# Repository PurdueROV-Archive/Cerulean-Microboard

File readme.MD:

This is an example repository of the previous Microboard for the ROV.

The Microboard was the brains of the ROV.

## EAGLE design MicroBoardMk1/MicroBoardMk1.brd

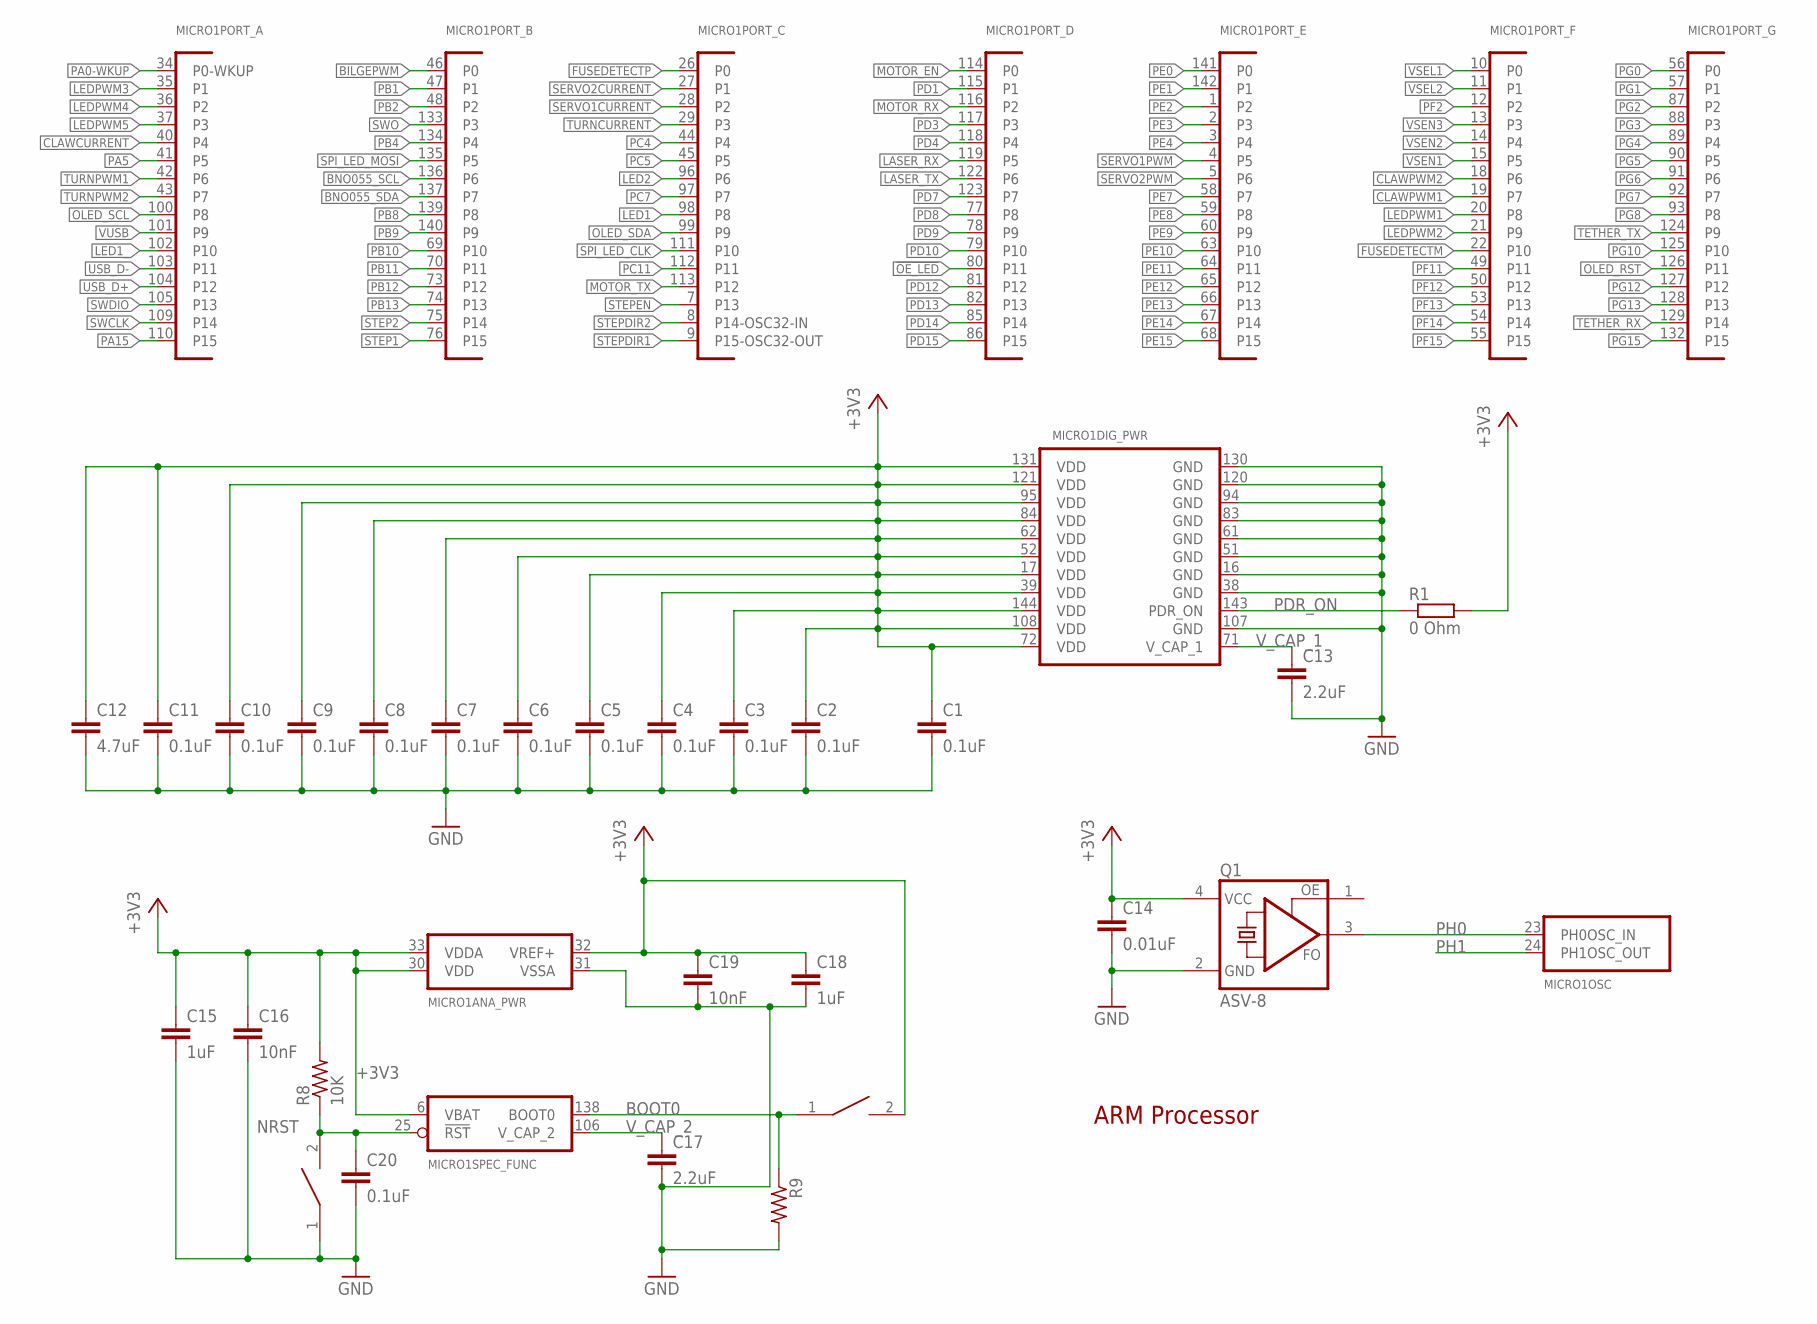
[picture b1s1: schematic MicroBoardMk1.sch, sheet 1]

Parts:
BOOT_SW: SWITCH; SW_2512
C1, C2, C3, C4, C5, C6, C7, C8, C9, C10, C11, C20: 0.1uF; C0603
C12: 4.7uF; C0603
C13, C17: 2.2uF; C0603
C14: 0.01uF; C0603
C15, C18: 1uF; C0603
C16, C19: 10nF; C0603
MICRO1: STM32F407ZET6; SQFP-S-20X20-144
Q1: ASV-8; ASF
R1: 0 Ohm; R0603
R8: 10K; R0603
R9: R-US_R0603; R0603
RST_SW: SWITCH; SW_2512

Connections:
!OE_LED: MICRO1.80 (P11); also elsewhere on the board
+3V3: BOOT_SW.2, C1.1, C2.1, C3.1, C4.1, C5.1, C6.1, C7.1, C8.1, C9.1, C10.1, C11.1, C12.1, C14.1, C15.1, C16.1, C18.1, C19.1, MICRO1.6 (VBAT), MICRO1.17 (VDD), MICRO1.30 (VDD), MICRO1.32 (VREF+), MICRO1.33 (VDDA), MICRO1.39 (VDD), MICRO1.52 (VDD), MICRO1.62 (VDD), MICRO1.72 (VDD), MICRO1.84 (VDD), MICRO1.95 (VDD), MICRO1.108 (VDD), MICRO1.121 (VDD), MICRO1.131 (VDD), MICRO1.144 (VDD), Q1.4 (VCC), R1.2, R8.2; also elsewhere on the board
BILGEPWM: MICRO1.46 (P0); also elsewhere on the board
BNO055_SCL: MICRO1.136 (P6); also elsewhere on the board
BNO055_SDA: MICRO1.137 (P7); also elsewhere on the board
BOOT0: BOOT_SW.1, MICRO1.138 (BOOT0), R9.1; also elsewhere on the board
CLAWCURRENT: MICRO1.40 (P4); also elsewhere on the board
CLAWPWM1: MICRO1.19 (P7); also elsewhere on the board
CLAWPWM2: MICRO1.18 (P6); also elsewhere on the board
FUSEDETECTM: MICRO1.22 (P10); also elsewhere on the board
FUSEDETECTP: MICRO1.26 (P0); also elsewhere on the board
GND: C1.2, C2.2, C3.2, C4.2, C5.2, C6.2, C7.2, C8.2, C9.2, C10.2, C11.2, C12.2, C13.2, C14.2, C15.2, C16.2, C17.2, C18.2, C19.2, C20.2, MICRO1.16 (GND), MICRO1.31 (VSSA), MICRO1.38 (GND), MICRO1.51 (GND), MICRO1.61 (GND), MICRO1.83 (GND), MICRO1.94 (GND), MICRO1.107 (GND), MICRO1.120 (GND), MICRO1.130 (GND), Q1.2 (GND), R9.2, RST_SW.1; also elsewhere on the board
LASER_RX: MICRO1.119 (P5); also elsewhere on the board
LASER_TX: MICRO1.122 (P6); also elsewhere on the board
LED1: MICRO1.98 (P8); also elsewhere on the board
LED1_: MICRO1.102 (P10); also elsewhere on the board
LED2: MICRO1.96 (P6); also elsewhere on the board
LEDPWM1: MICRO1.20 (P8); also elsewhere on the board
LEDPWM2: MICRO1.21 (P9); also elsewhere on the board
LEDPWM3: MICRO1.35 (P1); also elsewhere on the board
LEDPWM4: MICRO1.36 (P2); also elsewhere on the board
LEDPWM5: MICRO1.37 (P3); also elsewhere on the board
MOTOR_EN: MICRO1.114 (P0); also elsewhere on the board
MOTOR_RX: MICRO1.116 (P2); also elsewhere on the board
MOTOR_TX: MICRO1.113 (P12); also elsewhere on the board
NRST: C20.1, MICRO1.25 (!RST), R8.1, RST_SW.2; also elsewhere on the board
OLED_RST: MICRO1.126 (P11); also elsewhere on the board
OLED_SCL: MICRO1.100 (P8); also elsewhere on the board
OLED_SDA: MICRO1.99 (P9); also elsewhere on the board
PA0-WKUP: MICRO1.34 (P0-WKUP); also elsewhere on the board
PA5: MICRO1.41 (P5); also elsewhere on the board
PA15: MICRO1.110 (P15); also elsewhere on the board
PB1: MICRO1.47 (P1); also elsewhere on the board
PB2: MICRO1.48 (P2); also elsewhere on the board
PB4: MICRO1.134 (P4); also elsewhere on the board
PB8: MICRO1.139 (P8); also elsewhere on the board
PB9: MICRO1.140 (P9); also elsewhere on the board
PB10: MICRO1.69 (P10); also elsewhere on the board
PB11: MICRO1.70 (P11); also elsewhere on the board
PB12: MICRO1.73 (P12); also elsewhere on the board
PB13: MICRO1.74 (P13); also elsewhere on the board
PC4: MICRO1.44 (P4); also elsewhere on the board
PC5: MICRO1.45 (P5); also elsewhere on the board
PC7: MICRO1.97 (P7); also elsewhere on the board
PC11: MICRO1.112 (P11); also elsewhere on the board
PD1: MICRO1.115 (P1); also elsewhere on the board
PD3: MICRO1.117 (P3); also elsewhere on the board
PD4: MICRO1.118 (P4); also elsewhere on the board
PD7: MICRO1.123 (P7); also elsewhere on the board
PD8: MICRO1.77 (P8); also elsewhere on the board
PD9: MICRO1.78 (P9); also elsewhere on the board
PD10: MICRO1.79 (P10); also elsewhere on the board
PD12: MICRO1.81 (P12); also elsewhere on the board
PD13: MICRO1.82 (P13); also elsewhere on the board
PD14: MICRO1.85 (P14); also elsewhere on the board
PD15: MICRO1.86 (P15); also elsewhere on the board
PDR_ON: MICRO1.143 (PDR_ON), R1.1; also elsewhere on the board
PE0: MICRO1.141 (P0); also elsewhere on the board
PE1: MICRO1.142 (P1); also elsewhere on the board
PE2: MICRO1.1 (P2); also elsewhere on the board
PE3: MICRO1.2 (P3); also elsewhere on the board
PE4: MICRO1.3 (P4); also elsewhere on the board
PE7: MICRO1.58 (P7); also elsewhere on the board
PE8: MICRO1.59 (P8); also elsewhere on the board
PE9: MICRO1.60 (P9); also elsewhere on the board
PE10: MICRO1.63 (P10); also elsewhere on the board
PE11: MICRO1.64 (P11); also elsewhere on the board
PE12: MICRO1.65 (P12); also elsewhere on the board
PE13: MICRO1.66 (P13); also elsewhere on the board
PE14: MICRO1.67 (P14); also elsewhere on the board
PE15: MICRO1.68 (P15); also elsewhere on the board
PF2: MICRO1.12 (P2); also elsewhere on the board
PF11: MICRO1.49 (P11); also elsewhere on the board
PF12: MICRO1.50 (P12); also elsewhere on the board
PF13: MICRO1.53 (P13); also elsewhere on the board
PF14: MICRO1.54 (P14); also elsewhere on the board
PF15: MICRO1.55 (P15); also elsewhere on the board
PG0: MICRO1.56 (P0); also elsewhere on the board
PG1: MICRO1.57 (P1); also elsewhere on the board
PG2: MICRO1.87 (P2); also elsewhere on the board
PG3: MICRO1.88 (P3); also elsewhere on the board
PG4: MICRO1.89 (P4); also elsewhere on the board
PG5: MICRO1.90 (P5); also elsewhere on the board
PG6: MICRO1.91 (P6); also elsewhere on the board
PG7: MICRO1.92 (P7); also elsewhere on the board
PG8: MICRO1.93 (P8); also elsewhere on the board
PG10: MICRO1.125 (P10); also elsewhere on the board
PG12: MICRO1.127 (P12); also elsewhere on the board
PG13: MICRO1.128 (P13); also elsewhere on the board
PG15: MICRO1.132 (P15); also elsewhere on the board
PH0: MICRO1.23 (PH0OSC_IN), Q1.3 (FO); also elsewhere on the board
PH1: MICRO1.24 (PH1OSC_OUT); also elsewhere on the board
SERVO1CURRENT: MICRO1.28 (P2); also elsewhere on the board
SERVO1PWM: MICRO1.4 (P5); also elsewhere on the board
SERVO2CURRENT: MICRO1.27 (P1); also elsewhere on the board
SERVO2PWM: MICRO1.5 (P6); also elsewhere on the board
SPI_LED_CLK: MICRO1.111 (P10); also elsewhere on the board
SPI_LED_MOSI: MICRO1.135 (P5); also elsewhere on the board
STEP1: MICRO1.76 (P15); also elsewhere on the board
STEP2: MICRO1.75 (P14); also elsewhere on the board
STEPDIR1: MICRO1.9 (P15-OSC32-OUT); also elsewhere on the board
STEPDIR2: MICRO1.8 (P14-OSC32-IN); also elsewhere on the board
STEPEN: MICRO1.7 (P13); also elsewhere on the board
SWCLK: MICRO1.109 (P14); also elsewhere on the board
SWDIO: MICRO1.105 (P13); also elsewhere on the board
SWO: MICRO1.133 (P3); also elsewhere on the board
TETHER_RX: MICRO1.129 (P14); also elsewhere on the board
TETHER_TX: MICRO1.124 (P9); also elsewhere on the board
TURNCURRENT: MICRO1.29 (P3); also elsewhere on the board
TURNPWM1: MICRO1.42 (P6); also elsewhere on the board
TURNPWM2: MICRO1.43 (P7); also elsewhere on the board
USB_D+: MICRO1.104 (P12); also elsewhere on the board
USB_D-: MICRO1.103 (P11); also elsewhere on the board
VSEL1: MICRO1.10 (P0); also elsewhere on the board
VSEL2: MICRO1.11 (P1); also elsewhere on the board
VSEN1: MICRO1.15 (P5); also elsewhere on the board
VSEN2: MICRO1.14 (P4); also elsewhere on the board
VSEN3: MICRO1.13 (P3); also elsewhere on the board
VUSB: MICRO1.101 (P9); also elsewhere on the board
V_CAP_1: C13.1, MICRO1.71 (V_CAP_1); also elsewhere on the board
V_CAP_2: C17.1, MICRO1.106 (V_CAP_2); also elsewhere on the board

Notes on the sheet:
ARM Processor

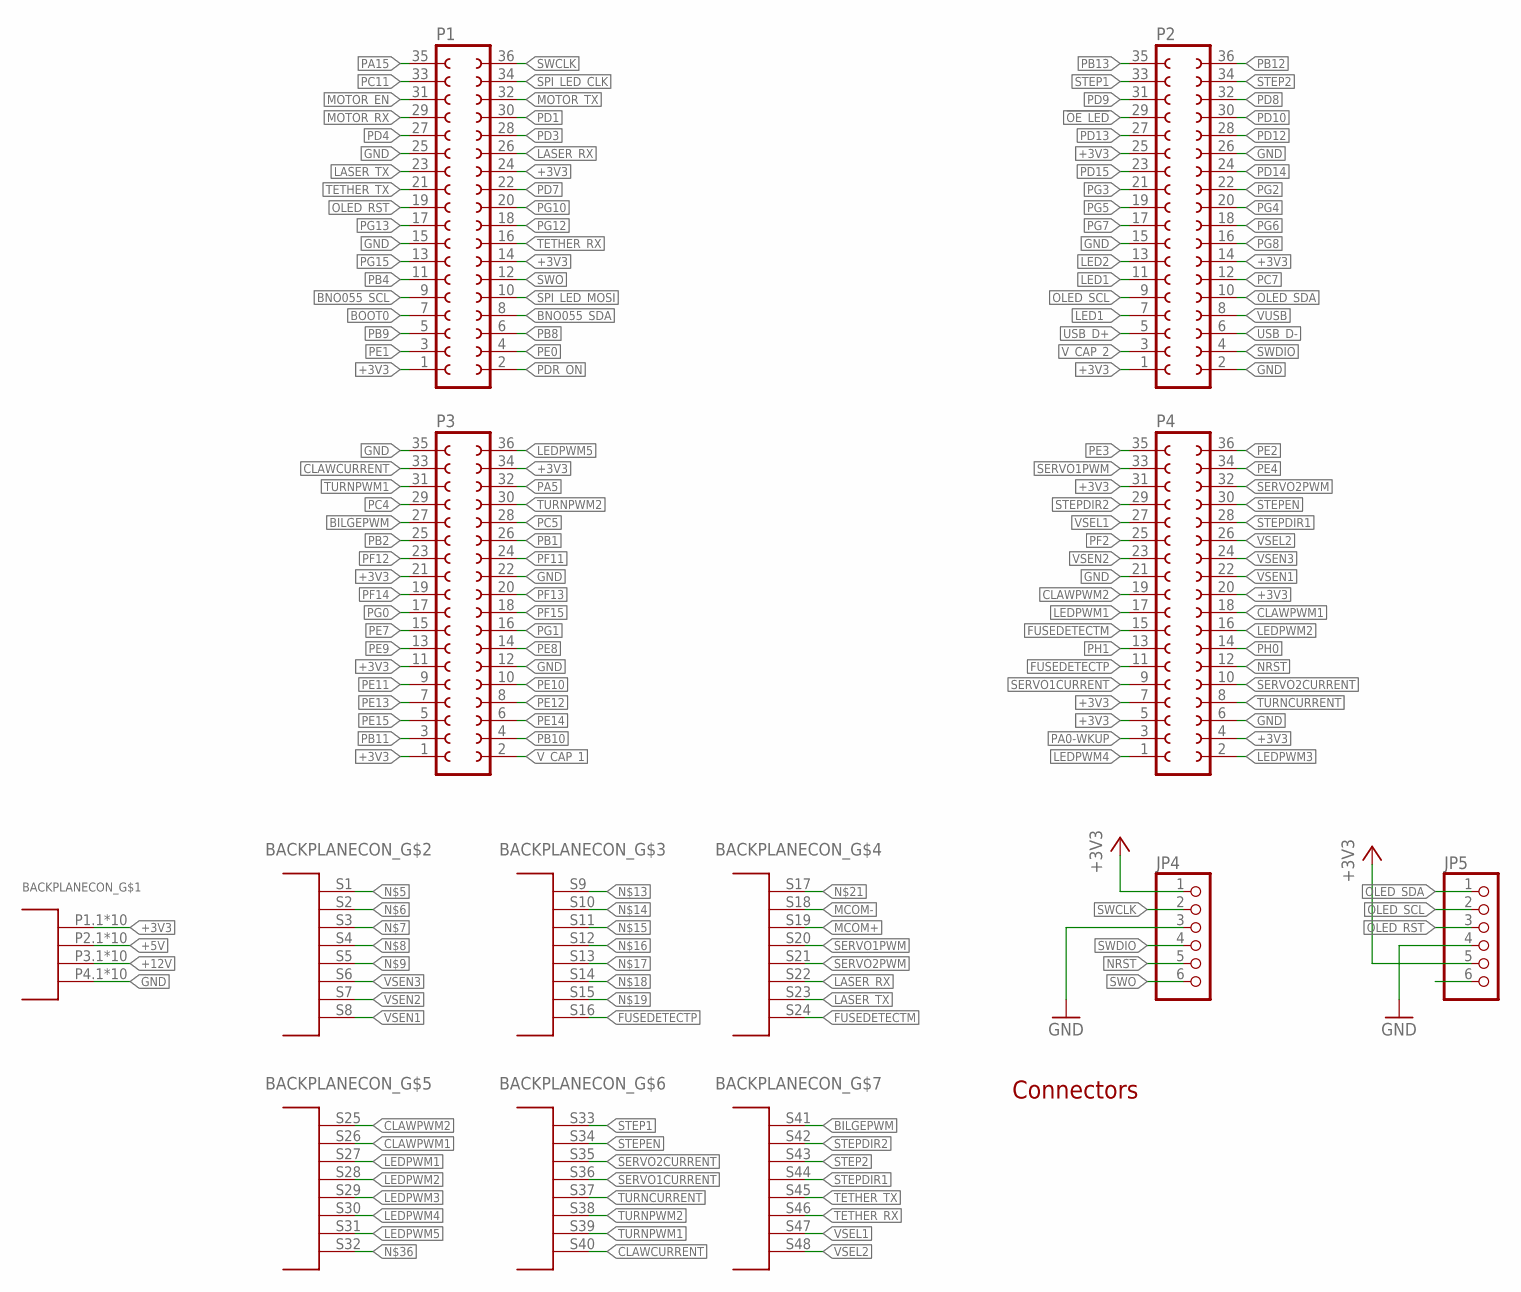
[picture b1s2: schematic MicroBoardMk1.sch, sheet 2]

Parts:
BACKPLANECON_: TEN60-S24-S24-P4-RA
JP4, JP5: PINHD-1X6; 1X06
P1, P2, P3, P4: FE18-2

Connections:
!OE_LED: P2.29; also elsewhere on the board
+3V3: BACKPLANECON_.P1.1, BACKPLANECON_.P1.2, BACKPLANECON_.P1.3, BACKPLANECON_.P1.4, BACKPLANECON_.P1.5, BACKPLANECON_.P1.6, BACKPLANECON_.P1.7, BACKPLANECON_.P1.8, BACKPLANECON_.P1.9, BACKPLANECON_.P1.10, JP4.1, JP5.5, P1.1, P1.14, P1.24, P2.1, P2.14, P2.25, P3.1, P3.11, P3.21, P3.34, P4.4, P4.5, P4.7, P4.20, P4.31; also elsewhere on the board
+5V: BACKPLANECON_.P2.1, BACKPLANECON_.P2.2, BACKPLANECON_.P2.3, BACKPLANECON_.P2.4, BACKPLANECON_.P2.5, BACKPLANECON_.P2.6, BACKPLANECON_.P2.7, BACKPLANECON_.P2.8, BACKPLANECON_.P2.9, BACKPLANECON_.P2.10; also elsewhere on the board
+12V: BACKPLANECON_.P3.1, BACKPLANECON_.P3.2, BACKPLANECON_.P3.3, BACKPLANECON_.P3.4, BACKPLANECON_.P3.5, BACKPLANECON_.P3.6, BACKPLANECON_.P3.7, BACKPLANECON_.P3.8, BACKPLANECON_.P3.9, BACKPLANECON_.P3.10
BILGEPWM: BACKPLANECON_.S41, P3.27; also elsewhere on the board
BNO055_SCL: P1.9; also elsewhere on the board
BNO055_SDA: P1.8; also elsewhere on the board
BOOT0: P1.7; also elsewhere on the board
CLAWCURRENT: BACKPLANECON_.S40, P3.33; also elsewhere on the board
CLAWPWM1: BACKPLANECON_.S26, P4.18; also elsewhere on the board
CLAWPWM2: BACKPLANECON_.S25, P4.19; also elsewhere on the board
FUSEDETECTM: BACKPLANECON_.S24, P4.15; also elsewhere on the board
FUSEDETECTP: BACKPLANECON_.S16, P4.11; also elsewhere on the board
GND: BACKPLANECON_.P4.1, BACKPLANECON_.P4.2, BACKPLANECON_.P4.3, BACKPLANECON_.P4.4, BACKPLANECON_.P4.5, BACKPLANECON_.P4.6, BACKPLANECON_.P4.7, BACKPLANECON_.P4.8, BACKPLANECON_.P4.9, BACKPLANECON_.P4.10, JP4.3, JP5.4, P1.15, P1.25, P2.2, P2.15, P2.26, P3.12, P3.22, P3.35, P4.6, P4.21; also elsewhere on the board
LASER_RX: BACKPLANECON_.S22, P1.26; also elsewhere on the board
LASER_TX: BACKPLANECON_.S23, P1.23; also elsewhere on the board
LED1: P2.11; also elsewhere on the board
LED1_: P2.7; also elsewhere on the board
LED2: P2.13; also elsewhere on the board
LEDPWM1: BACKPLANECON_.S27, P4.17; also elsewhere on the board
LEDPWM2: BACKPLANECON_.S28, P4.16; also elsewhere on the board
LEDPWM3: BACKPLANECON_.S29, P4.2; also elsewhere on the board
LEDPWM4: BACKPLANECON_.S30, P4.1; also elsewhere on the board
LEDPWM5: BACKPLANECON_.S31, P3.36; also elsewhere on the board
MCOM+: BACKPLANECON_.S19; also elsewhere on the board
MCOM-: BACKPLANECON_.S18; also elsewhere on the board
MOTOR_EN: P1.31; also elsewhere on the board
MOTOR_RX: P1.29; also elsewhere on the board
MOTOR_TX: P1.32; also elsewhere on the board
NRST: JP4.5, P4.12; also elsewhere on the board
OLED_RST: JP5.3, P1.19; also elsewhere on the board
OLED_SCL: JP5.2, P2.9; also elsewhere on the board
OLED_SDA: JP5.1, P2.10; also elsewhere on the board
PA0-WKUP: P4.3; also elsewhere on the board
PA5: P3.32; also elsewhere on the board
PA15: P1.35; also elsewhere on the board
PB1: P3.26; also elsewhere on the board
PB2: P3.25; also elsewhere on the board
PB4: P1.11; also elsewhere on the board
PB8: P1.6; also elsewhere on the board
PB9: P1.5; also elsewhere on the board
PB10: P3.4; also elsewhere on the board
PB11: P3.3; also elsewhere on the board
PB12: P2.36; also elsewhere on the board
PB13: P2.35; also elsewhere on the board
PC4: P3.29; also elsewhere on the board
PC5: P3.28; also elsewhere on the board
PC7: P2.12; also elsewhere on the board
PC11: P1.33; also elsewhere on the board
PD1: P1.30; also elsewhere on the board
PD3: P1.28; also elsewhere on the board
PD4: P1.27; also elsewhere on the board
PD7: P1.22; also elsewhere on the board
PD8: P2.32; also elsewhere on the board
PD9: P2.31; also elsewhere on the board
PD10: P2.30; also elsewhere on the board
PD12: P2.28; also elsewhere on the board
PD13: P2.27; also elsewhere on the board
PD14: P2.24; also elsewhere on the board
PD15: P2.23; also elsewhere on the board
PDR_ON: P1.2; also elsewhere on the board
PE0: P1.4; also elsewhere on the board
PE1: P1.3; also elsewhere on the board
PE2: P4.36; also elsewhere on the board
PE3: P4.35; also elsewhere on the board
PE4: P4.34; also elsewhere on the board
PE7: P3.15; also elsewhere on the board
PE8: P3.14; also elsewhere on the board
PE9: P3.13; also elsewhere on the board
PE10: P3.10; also elsewhere on the board
PE11: P3.9; also elsewhere on the board
PE12: P3.8; also elsewhere on the board
PE13: P3.7; also elsewhere on the board
PE14: P3.6; also elsewhere on the board
PE15: P3.5; also elsewhere on the board
PF2: P4.25; also elsewhere on the board
PF11: P3.24; also elsewhere on the board
PF12: P3.23; also elsewhere on the board
PF13: P3.20; also elsewhere on the board
PF14: P3.19; also elsewhere on the board
PF15: P3.18; also elsewhere on the board
PG0: P3.17; also elsewhere on the board
PG1: P3.16; also elsewhere on the board
PG2: P2.22; also elsewhere on the board
PG3: P2.21; also elsewhere on the board
PG4: P2.20; also elsewhere on the board
PG5: P2.19; also elsewhere on the board
PG6: P2.18; also elsewhere on the board
PG7: P2.17; also elsewhere on the board
PG8: P2.16; also elsewhere on the board
PG10: P1.20; also elsewhere on the board
PG12: P1.18; also elsewhere on the board
PG13: P1.17; also elsewhere on the board
PG15: P1.13; also elsewhere on the board
PH0: P4.14; also elsewhere on the board
PH1: P4.13; also elsewhere on the board
SERVO1CURRENT: BACKPLANECON_.S36, P4.9; also elsewhere on the board
SERVO1PWM: BACKPLANECON_.S20, P4.33; also elsewhere on the board
SERVO2CURRENT: BACKPLANECON_.S35, P4.10; also elsewhere on the board
SERVO2PWM: BACKPLANECON_.S21, P4.32; also elsewhere on the board
SPI_LED_CLK: P1.34; also elsewhere on the board
SPI_LED_MOSI: P1.10; also elsewhere on the board
STEP1: BACKPLANECON_.S33, P2.33; also elsewhere on the board
STEP2: BACKPLANECON_.S43, P2.34; also elsewhere on the board
STEPDIR1: BACKPLANECON_.S44, P4.28; also elsewhere on the board
STEPDIR2: BACKPLANECON_.S42, P4.29; also elsewhere on the board
STEPEN: BACKPLANECON_.S34, P4.30; also elsewhere on the board
SWCLK: JP4.2, P1.36; also elsewhere on the board
SWDIO: JP4.4, P2.4; also elsewhere on the board
SWO: JP4.6, P1.12; also elsewhere on the board
TETHER_RX: BACKPLANECON_.S46, P1.16; also elsewhere on the board
TETHER_TX: BACKPLANECON_.S45, P1.21; also elsewhere on the board
TURNCURRENT: BACKPLANECON_.S37, P4.8; also elsewhere on the board
TURNPWM1: BACKPLANECON_.S39, P3.31; also elsewhere on the board
TURNPWM2: BACKPLANECON_.S38, P3.30; also elsewhere on the board
USB_D+: P2.5; also elsewhere on the board
USB_D-: P2.6; also elsewhere on the board
VSEL1: BACKPLANECON_.S47, P4.27; also elsewhere on the board
VSEL2: BACKPLANECON_.S48, P4.26; also elsewhere on the board
VSEN1: BACKPLANECON_.S8, P4.22; also elsewhere on the board
VSEN2: BACKPLANECON_.S7, P4.23; also elsewhere on the board
VSEN3: BACKPLANECON_.S6, P4.24; also elsewhere on the board
VUSB: P2.8; also elsewhere on the board
V_CAP_1: P3.2; also elsewhere on the board
V_CAP_2: P2.3; also elsewhere on the board

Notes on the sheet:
Connectors

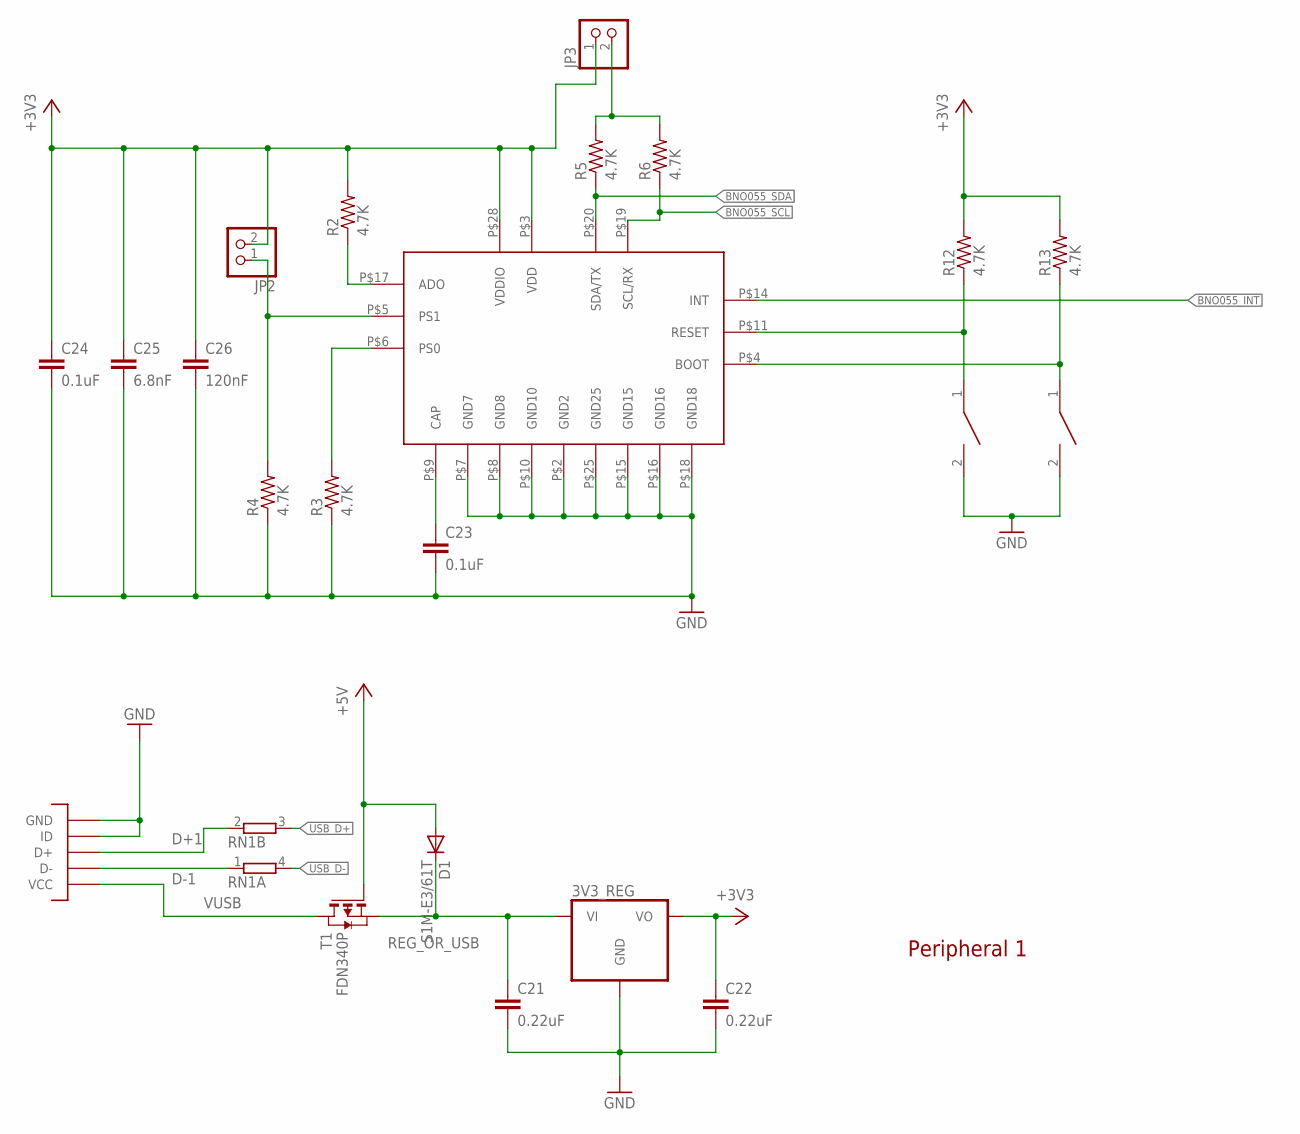
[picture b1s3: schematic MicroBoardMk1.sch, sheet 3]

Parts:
3V3_REG: AP1117-3.3SOT223; SOT223
BNO055: BNO055; LGA28
BNO_BOOT_SW: SWITCH; SW_2512
BNO_RST_SW: SWITCH; SW_2512
C21, C22: 0.22uF; C0603
C23, C24: 0.1uF; C0603
C25: 6.8nF; C0603
C26: 120nF; C0603
D1: S1M-E3/61T; DO-214AC
JP1: MICROUSB; MICRO_B
JP2, JP3: PINHD-1X2; 1X02
R2, R3, R4, R5, R6, R12, R13: 4.7K; R0603
RN1: 2R-NEXBV4V; EXBV4V
T1: FDN340P; SOT-23

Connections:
+3V3: 3V3_REG.2 (VO), 3V3_REG.4 (VO), BNO055.P$3 (VDD), BNO055.P$28 (VDDIO), C22.1, C24.1, C25.1, C26.1, JP2.2, JP3.1, R2.2, R12.2, R13.2; also elsewhere on the board
+5V: D1.A, T1.3 (G); also elsewhere on the board
BNO055_INT: BNO055.P$14 (INT)
BNO055_SCL: BNO055.P$19 (SCL/RX), R6.1; also elsewhere on the board
BNO055_SDA: BNO055.P$20 (SDA/TX), R5.1; also elsewhere on the board
D+1: JP1.P3 (D+), RN1.2 (1)
D-1: JP1.P2 (D-), RN1.1
GND: 3V3_REG.1 (GND), BNO055.P$2 (GND2), BNO055.P$7 (GND7), BNO055.P$8 (GND8), BNO055.P$10 (GND10), BNO055.P$15 (GND15), BNO055.P$16 (GND16), BNO055.P$18 (GND18), BNO055.P$25 (GND25), BNO_BOOT_SW.2, BNO_RST_SW.2, C21.2, C22.2, C23.2, C24.2, C25.2, C26.2, JP1.GND1 (GND), JP1.GND2 (GND), JP1.GND3 (GND), JP1.GND4 (GND), JP1.GND7 (GND), JP1.GND8 (GND), JP1.P4 (ID), JP1.P5 (GND), R3.1, R4.1; also elsewhere on the board
unnamed: BNO055.P$9 (CAP), C23.1
unnamed: BNO055.P$17 (ADO), R2.1
unnamed: BNO055.P$5 (PS1), JP2.1, R4.2
unnamed: BNO055.P$6 (PS0), R3.2
unnamed: JP3.2, R5.2, R6.2
unnamed: BNO055.P$4 (BOOT), BNO_BOOT_SW.1, R13.1
unnamed: BNO055.P$11 (RESET), BNO_RST_SW.1, R12.1
REG_OR_USB: 3V3_REG.3 (VI), C21.1, D1.C, T1.2 (S)
USB_D+: RN1.3 (2); also elsewhere on the board
USB_D-: RN1.4 (2); also elsewhere on the board
VUSB: JP1.P1 (VCC), T1.1 (D); also elsewhere on the board

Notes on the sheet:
Peripheral 1

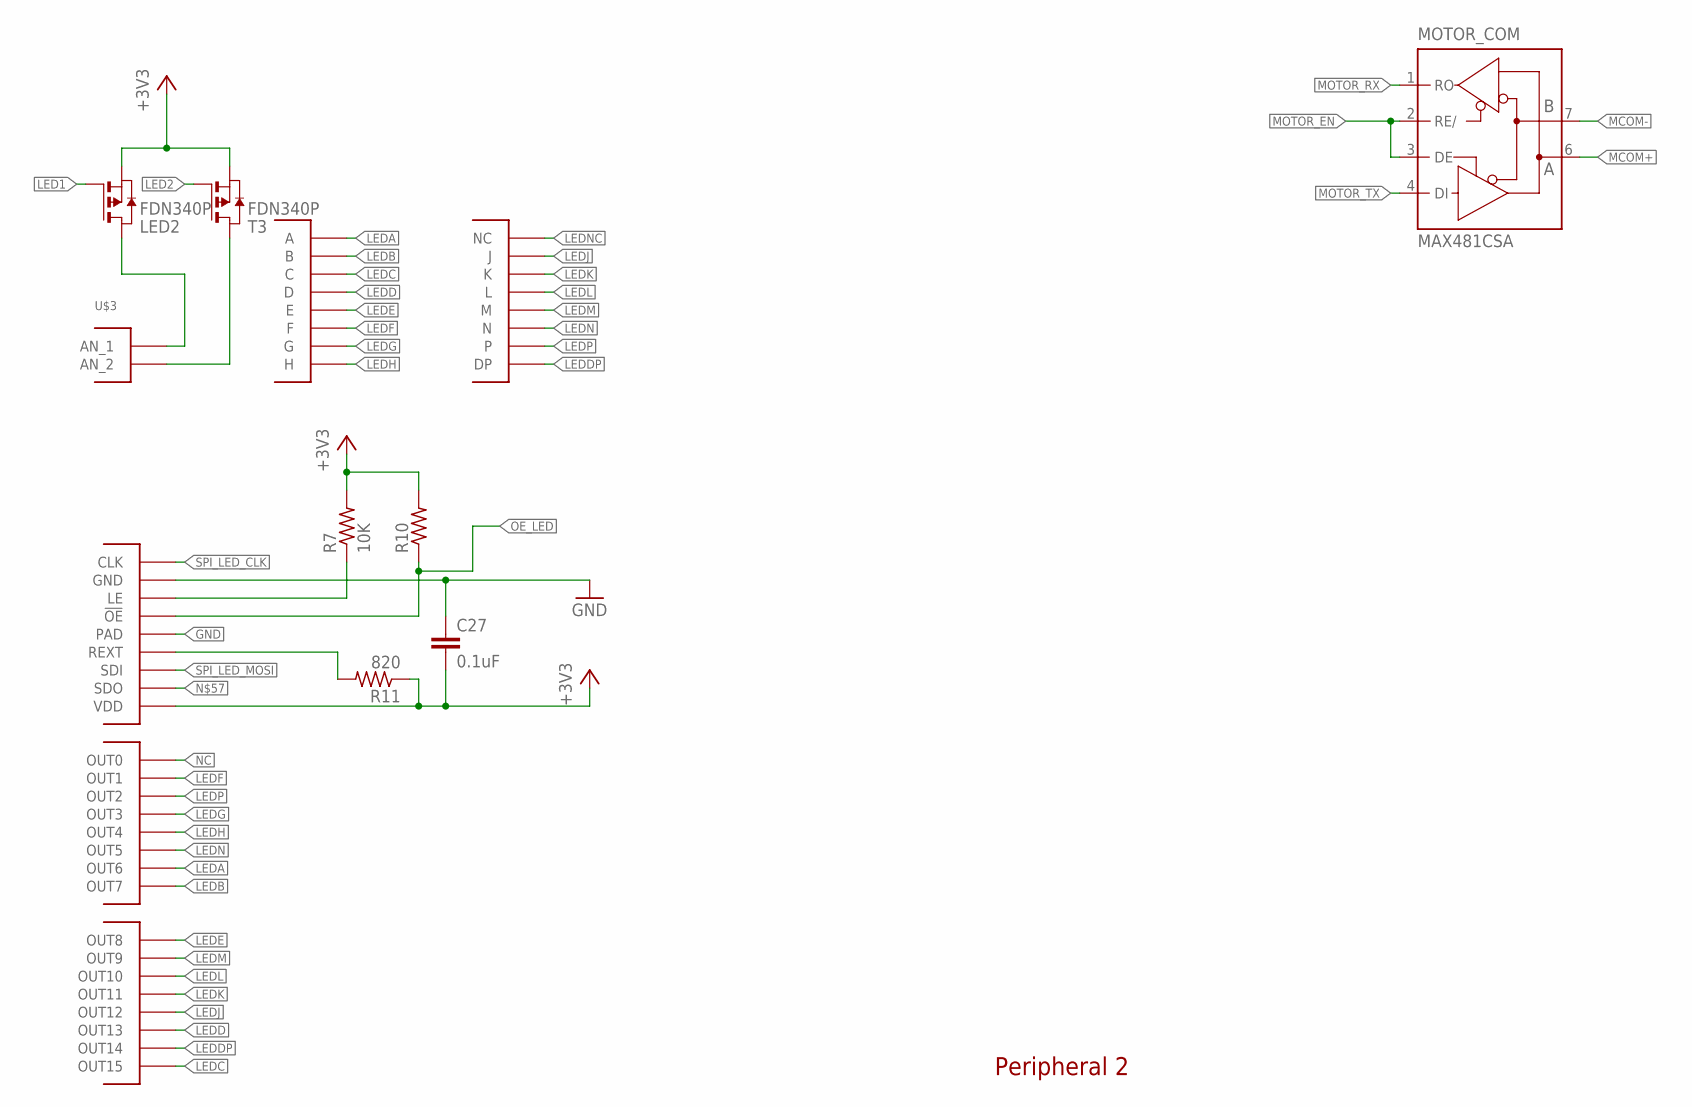
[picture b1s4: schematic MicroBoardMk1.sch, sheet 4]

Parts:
A6282: A6282; TSSOP24
C27: 0.1uF; C0603
LED2: FDN340P; SOT-23
MOTOR_COM: MAX481CSA; SO08
R7: 10K; R0603
R10: R-US_R0603; R0603
R11: 820; R0603
T3: FDN340P; SOT-23
U$3: LEDDISP

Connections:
!OE_LED: A6282.21 (!OE), R10.1; also elsewhere on the board
+3V3: A6282.24 (VDD), C27.2, LED2.2 (S), R7.2, R10.2, R11.1, T3.2 (S); also elsewhere on the board
GND: A6282.1 (GND), A6282.PAD, C27.1, MOTOR_COM.5 (GND); also elsewhere on the board
LED1: LED2.3 (G); also elsewhere on the board
LED2: T3.3 (G); also elsewhere on the board
LEDA: A6282.11 (OUT6), U$3.P$12 (A)
LEDB: A6282.12 (OUT7), U$3.P$10 (B)
LEDC: A6282.20 (OUT15), U$3.P$9 (C)
LEDD: A6282.18 (OUT13), U$3.P$7 (D)
LEDDP: A6282.19 (OUT14), U$3.P$8 (DP)
LEDE: A6282.13 (OUT8), U$3.P$1 (E)
LEDF: A6282.6 (OUT1), U$3.P$18 (F)
LEDG: A6282.8 (OUT3), U$3.P$15 (G)
LEDH: A6282.9 (OUT4), U$3.P$14 (H)
LEDJ: A6282.17 (OUT12), U$3.P$6 (J)
LEDK: A6282.16 (OUT11), U$3.P$5 (K)
LEDL: A6282.15 (OUT10), U$3.P$4 (L)
LEDM: A6282.14 (OUT9), U$3.P$2 (M)
LEDN: A6282.10 (OUT5), U$3.P$13 (N)
LEDNC: U$3.P$3 (NC)
LEDP: A6282.7 (OUT2), U$3.P$17
MCOM+: MOTOR_COM.6 (A); also elsewhere on the board
MCOM-: MOTOR_COM.7 (B); also elsewhere on the board
MOTOR_EN: MOTOR_COM.2 (RE/), MOTOR_COM.3 (DE); also elsewhere on the board
MOTOR_RX: MOTOR_COM.1 (RO); also elsewhere on the board
MOTOR_TX: MOTOR_COM.4 (DI); also elsewhere on the board
unnamed: T3.1 (D), U$3.P$11 (AN_2)
unnamed: LED2.1 (D), U$3.P$16 (AN_1)
unnamed: A6282.4 (LE), R7.1
unnamed: A6282.23 (REXT), R11.2
NC: A6282.5 (OUT0)
SPI_LED_CLK: A6282.3 (CLK); also elsewhere on the board
SPI_LED_MOSI: A6282.2 (SDI); also elsewhere on the board
VCC: MOTOR_COM.8 (VCC)

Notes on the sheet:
Peripheral 2

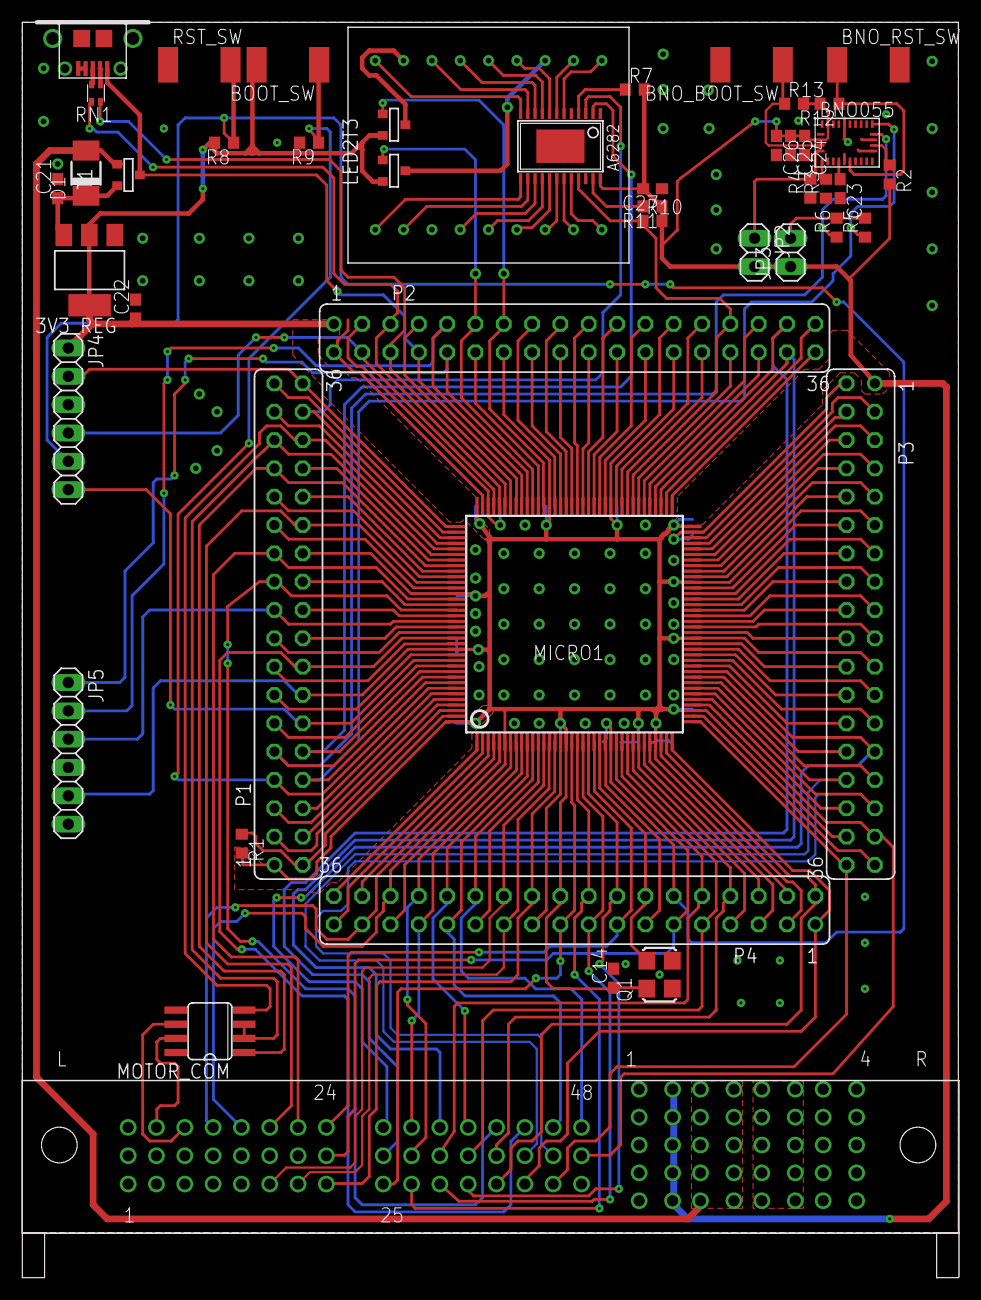
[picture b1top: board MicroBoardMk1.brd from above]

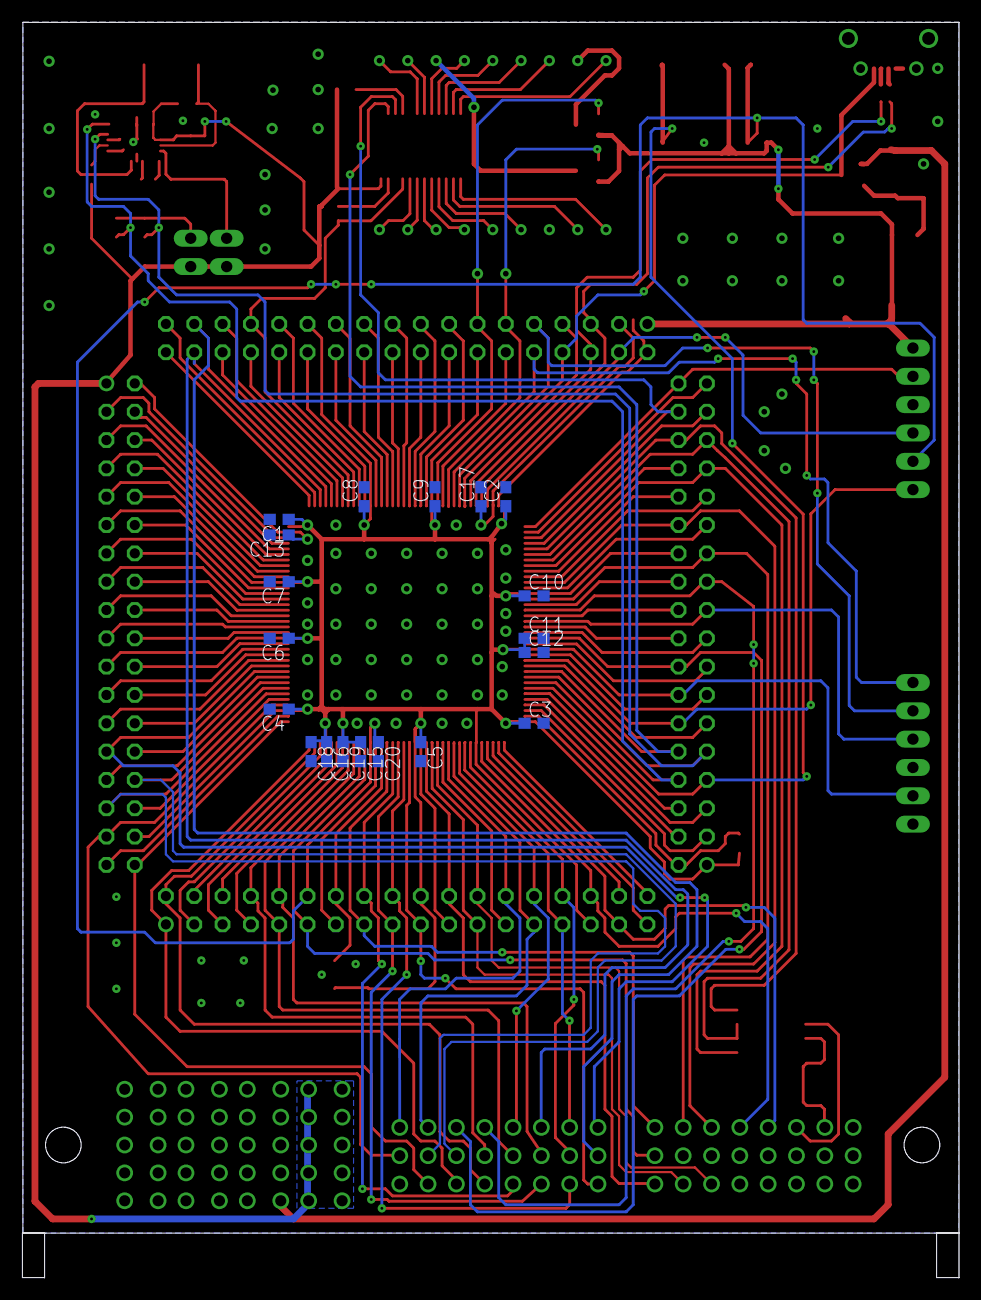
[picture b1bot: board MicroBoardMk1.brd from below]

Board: 2 copper layers, 84.0 x 112.6 mm, 66 parts (19 on the bottom side), 154 nets.

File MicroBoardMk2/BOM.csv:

Qty,Value,Device,Package,Parts,Description,,,,,,,,,1,,2R-NEXBV4V,EXBV4V,RN1,Array Chip Resistor,,,,,,,,,4,,FE18-2,FE18-2,P1,,,,,,,,,,4,,LED0603,LED-0603,BLU,,,,,,,,,,2,,M02PTH,1X02,JP6,,,,,,,,,,3,,M06SILK_FEMALE_PTH,1X06,JP4,,,,,,,,,,1,,STM32F407ZET6,SQFP-S-20X20-144,MICRO1,168 MHz,,,,,,,,,1,0 Ohm,R-EU_R0603,R0603,R1,RESISTOR,,,,,,,,,1,0.01uF,C-EUC0603,C0603,C14,CAPACITOR,,,,,,,,,14,0.1uF,C-EUC0603,C0603,C1,,,, C9, C10, C11, C20, C23," C24"";""CAPACITOR"," European "";"""";"2,0.22uF,C-EUC0603,C0603,C21,,,,,,,,,,8,10K,R-US_R0603,R0603,R7,,,,,,,,,,2,10nF,C-EUC0603,C0603,C16,same as 0.01uF,,,,,,,,,1,120,R-US_R0603,R0603,R17,RESISTOR,,,,,,,,,1,120nF,C-EUC0603,C0603,C26,CAPACITOR,,,,,,,,,2,1uF,C-EUC0603,C0603,C15,,,,,,,,,,2,2.2uF,C-EUC0603,C0603,C13,,,,,,,,,,7,4.7K,R-US_R0603,R0603,R2,,,,,,,,,,1,4.7uF,C-EUC0603,C0603,C12,CAPACITOR,,,,,,,,,1,6.8nF,C-EUC0603,C0603,C25,CAPACITOR,,,,,,,,,1,AP1117-3.3SOT223,AP1117-3.3SOT223,SOT223,3V3_REG,http://www.digikey.c,,,,,,,,,1,ASV-8,ASF,ASF,Q1,CRYSTAL CLOCK OSCILL,,,,,,,,,1,BNO055,BNO055,LGA28,BNO055,,,,,,,,,,1,BSS138,BSS123,SOT23,T2,N-CHANNEL MOS FET,,,,,,,,,1,FDN340P,FDN340P,SOT-23,T1,MOS FET,,,,,,,,,1,MAX481CSA,MAX481CSA,SO08,MOTOR_COM,RS485 TRANSEIVER,,,,,,,,,1,MICROUSB,MICROUSB,MICRO_B,JP1,,,,,,,,,,1,S1M-E3/61T,DIODE-DO-214AC,DO-214AC,D1,DIODE,,,,,,,,,4,SWITCH,SWITCH,SW_2512,BNO_BOOT_SW,,,,,,,,,,1,TEN60-S24-S24-P4-RA,TEN60-S24-S24-P4-RA,TEN60-S24-S24-P4-RA,BACKPLANECON_,,,,,,,,,,1,WS2812B,WS2812B,WS2812B,L1,,,,,,,,,,

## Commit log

2015-09-24 adding old board as an example
2015-09-24 adding readme
